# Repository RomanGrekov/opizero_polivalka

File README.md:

# opizero_polivalka

# Ansible
# Check target host
ansible target -a "uptime" -c paramiko<br />

# Userfull links

http://opi-gpio.readthedocs.io/en/latest/api-documentation.html<br />
http://pillow.readthedocs.io/en/3.4.x/reference/ImageDraw.html<br />
https://nayon.fr/blog/ssd1306-monochrome-oled-display-on-orangepi-in-python/<br />
https://www.14core.com/wiring_the_i2c__spi_oled_monochrome_display_with_raspberrypi/<br />

# Network settings
/etc/wpa_supplicant/wpa_supplicant.conf<br />    
<br />
network={<br />
   ssid="Visonic"<br />
   proto=WPA2<br />
   psk="*******"<br />
   id_str="mywifi"<br />
}<br />
<br />
##############################################<br />
<br />
/etc/network/interfaces<br />
auto lo<br />
iface lo inet loopback<br />
<br />
allow-hotplug wlan0<br />
iface wlan0 inet manual<br />
wpa-roam /etc/wpa_supplicant/wpa_supplicant.conf <br />
iface mywifi inet dhcp<br />

or use nmcli<br />
iwconfig wlan0<br />
nmcli dev wifi list<br />
nmcli device wifi connect MYHOME password 'p@55w0rd'<br />
nmcli radio wifi<br />
nmcli radio wifi <on|off><br />
nmcli device wifi rescan<br />

#############################################<br />

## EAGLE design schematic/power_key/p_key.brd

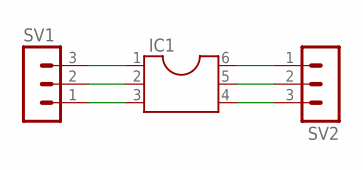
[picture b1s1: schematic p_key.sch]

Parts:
IC1: DIL6; DIL06
SV1, SV2: MA03-1

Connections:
unnamed: IC1.1, SV1.3
unnamed: IC1.2, SV1.2
unnamed: IC1.3, SV1.1
unnamed: IC1.6, SV2.1
unnamed: IC1.5, SV2.2
unnamed: IC1.4, SV2.3

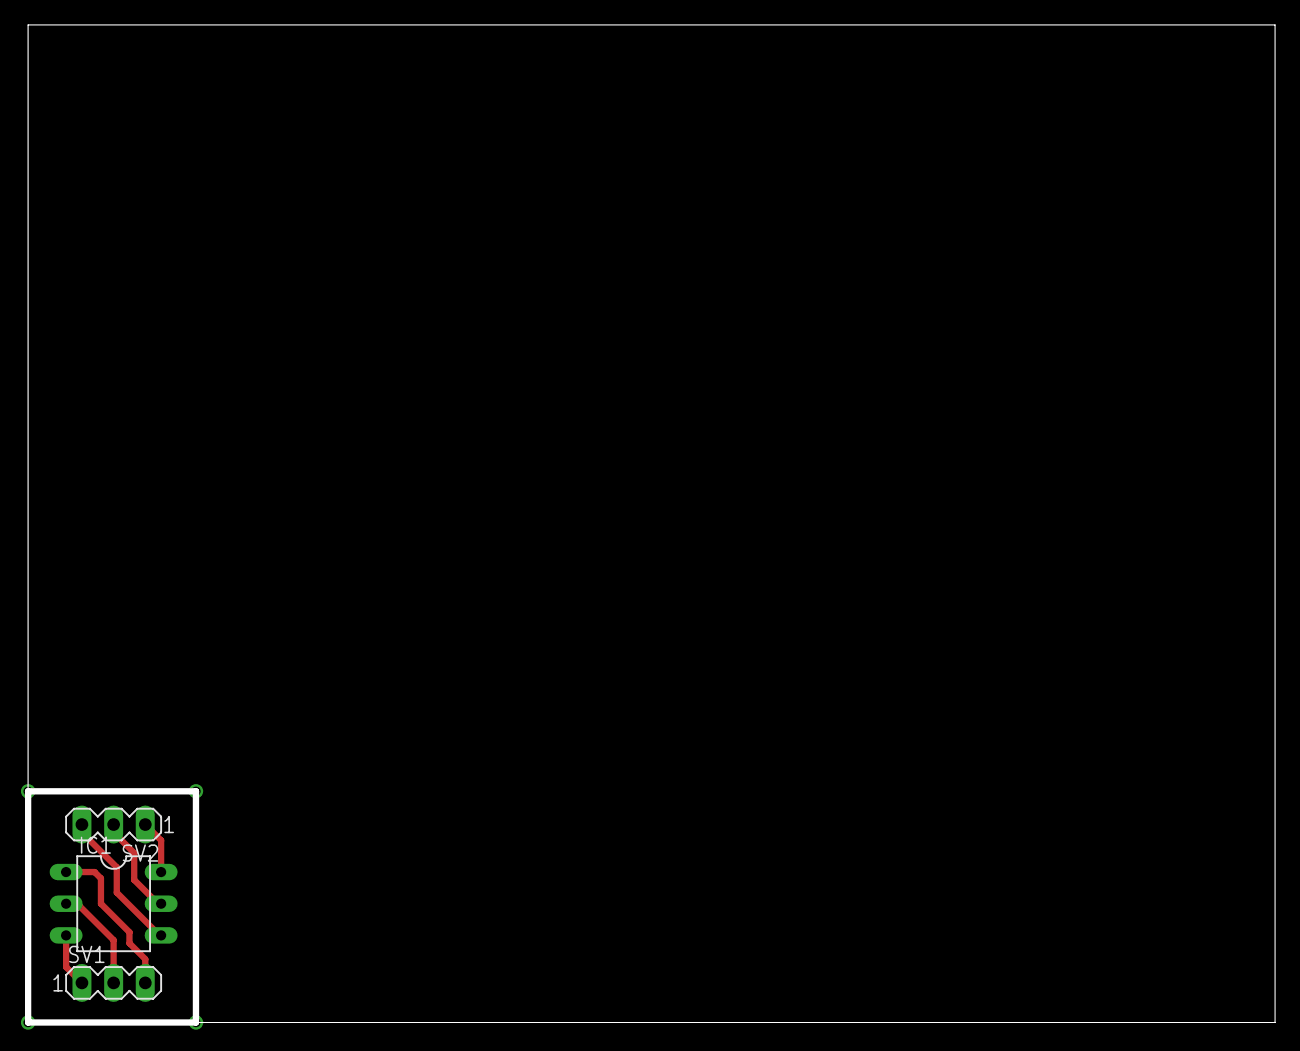
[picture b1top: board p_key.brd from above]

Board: 2 copper layers, 100.0 x 80.0 mm, 3 parts (0 on the bottom side), 6 nets.

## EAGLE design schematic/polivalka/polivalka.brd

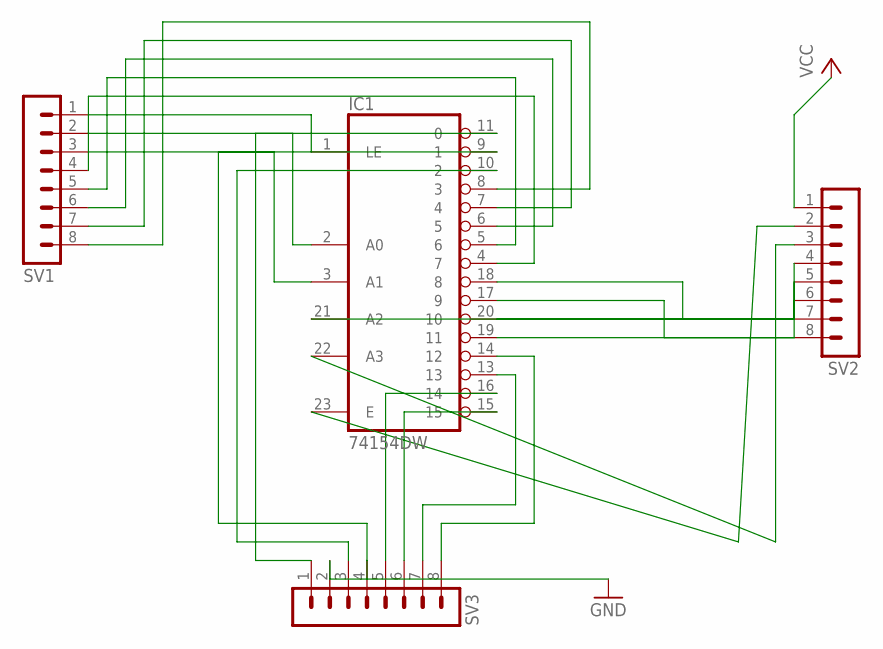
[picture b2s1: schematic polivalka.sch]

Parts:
IC1: 74154DW; SO24W
SV1, SV2, SV3: MA08-1

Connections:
GND: IC1.12 (GND), SV3.2
unnamed: IC1.1 (LE), SV1.1
unnamed: IC1.2 (A0), SV1.2
unnamed: IC1.3 (A1), SV1.3
unnamed: IC1.4 (7), SV1.4
unnamed: IC1.5 (6), SV1.5
unnamed: IC1.6 (5), SV1.6
unnamed: IC1.7 (4), SV1.7
unnamed: IC1.8 (3), SV1.8
unnamed: IC1.11 (0), SV3.1
unnamed: IC1.9 (1), SV3.4
unnamed: IC1.10 (2), SV3.3
unnamed: IC1.14 (12), SV3.8
unnamed: IC1.13, SV3.7
unnamed: IC1.15, SV3.6
unnamed: IC1.16 (14), SV3.5
unnamed: IC1.17 (9), SV2.8
unnamed: IC1.18 (8), SV2.7
unnamed: IC1.19 (11), SV2.6
unnamed: IC1.20 (10), SV2.5
unnamed: IC1.21 (A2), SV2.4
unnamed: IC1.22 (A3), SV2.3
unnamed: IC1.23 (E), SV2.2
VCC: IC1.24 (VCC), SV2.1

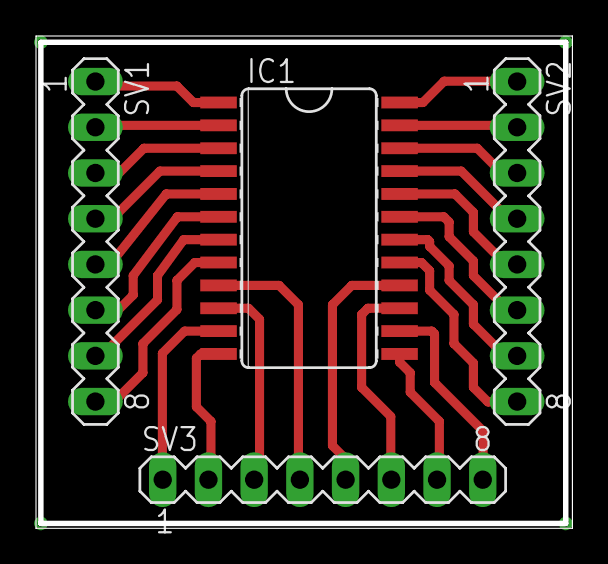
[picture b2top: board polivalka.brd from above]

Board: 2 copper layers, 29.8 x 27.4 mm, 4 parts (0 on the bottom side), 24 nets.

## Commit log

2017-09-02 Added network settings for opi zero
2017-09-02 Added nl to readme
2017-09-02 Added flask import
2017-09-02 Added multiplexor
2017-09-04 Finished multiplexor
2017-09-04 Finished multiplexor, fully
2018-03-22 Update README.md
    added alternative wifi sertup
